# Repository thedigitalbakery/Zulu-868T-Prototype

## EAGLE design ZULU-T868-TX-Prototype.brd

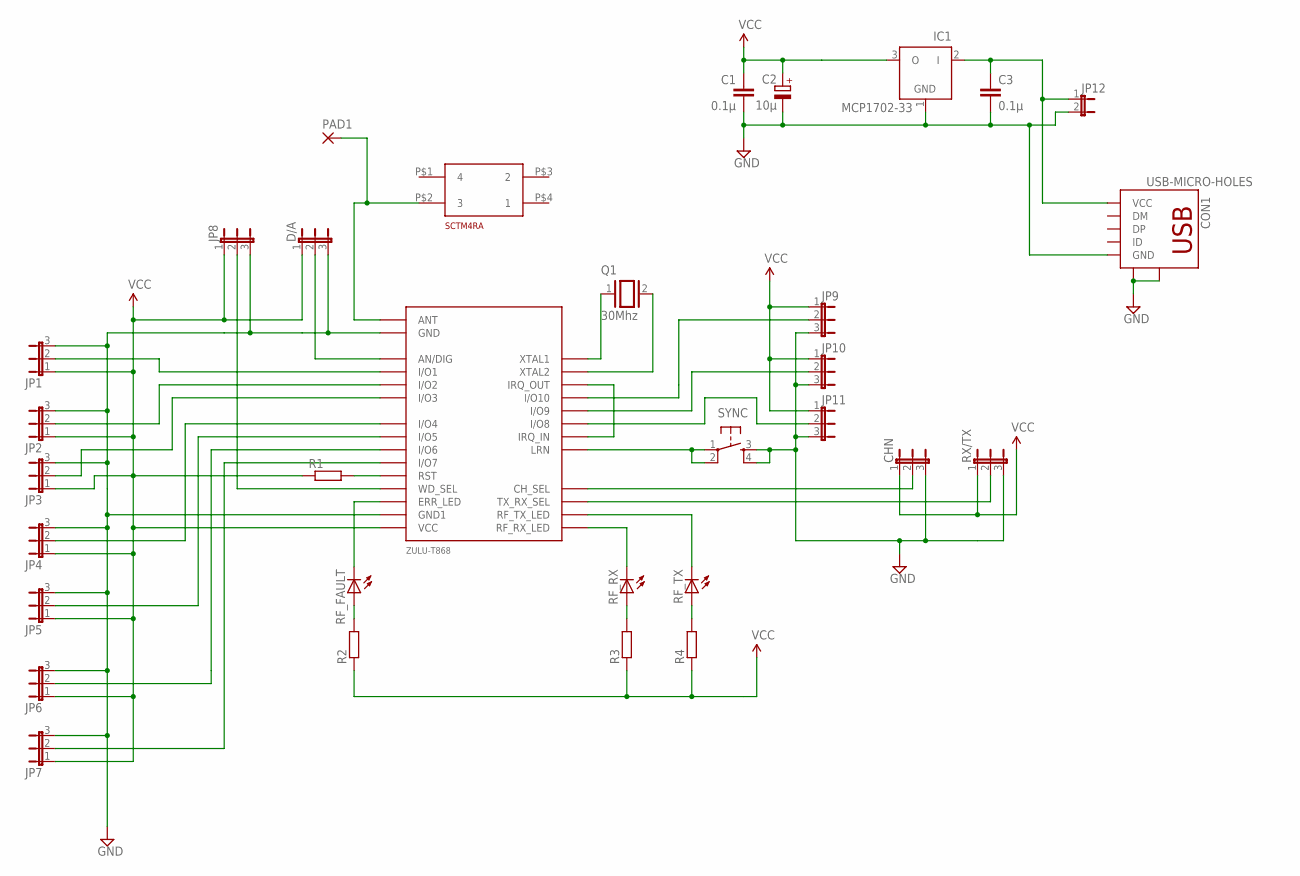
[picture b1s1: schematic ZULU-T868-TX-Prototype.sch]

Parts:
C1, C3: 0.1µ; C0805
C2: 10µ; E1,8-4
CHN: JP2E; JP2
CON1: USB-MICRO-HOLES; MICRO-USB-B-HOLES
D/A: JP2E; JP2
IC1: MCP1702-33; TO92
JP1, JP2, JP3, JP4, JP5, JP6, JP7, JP8, JP9, JP10, JP11: JP2E; JP2
JP12: JP1E; JP1
PAD1: 1,6/0,8
Q1: 30Mhz; QS
R1, R2, R3, R4: R-EU_M0805; M0805
RF_FAULT: LEDCHIPLED_0805; CHIPLED_0805
RF_RX: LEDCHIPLED_0805; CHIPLED_0805
RF_TX: LEDCHIPLED_0805; CHIPLED_0805
RX/TX: JP2E; JP2
SYNC: TAC_SWITCHPTH; TACTILE-PTH
U$1: SCTM4RA
U$2: ZULU-T868; ZULU-T-MODULE

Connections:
GND: C1.2, C2.-, C3.2, CHN.3, CON1.P$5 (GND), CON1.SHIELD1, CON1.SHIELD2, D/A.3, IC1.1 (GND), JP1.3, JP2.3, JP3.3, JP4.3, JP5.3, JP6.3, JP7.3, JP8.3, JP9.3, JP10.3, JP11.3, JP12.2, RX/TX.3, SYNC.3, SYNC.4, U$2.P$2 (GND), U$2.P$15 (GND1)
unnamed: D/A.2, U$2.P$3 (AN/DIG)
unnamed: Q1.1, U$2.P$30 (XTAL1)
unnamed: Q1.2, U$2.P$29 (XTAL2)
unnamed: R1.2, U$2.P$12 (RST)
unnamed: CHN.2, U$2.P$20 (CH_SEL)
unnamed: U$2.P$24 (IRQ_IN), U$2.P$28 (IRQ_OUT)
unnamed: RX/TX.2, U$2.P$19 (TX_RX_SEL)
unnamed: SYNC.1, SYNC.2, U$2.P$23 (LRN)
unnamed: RF_FAULT.C, U$2.P$14 (ERR_LED)
unnamed: JP2.2, U$2.P$5 (I/O2)
unnamed: JP1.2, U$2.P$4 (I/O1)
unnamed: C3.1, CON1.P$1 (VCC), IC1.2 (I), JP12.1
unnamed: R3.2, RF_RX.A
unnamed: R4.2, RF_TX.A
unnamed: RF_RX.C, U$2.P$17 (RF_RX_LED)
unnamed: RF_TX.C, U$2.P$18 (RF_TX_LED)
unnamed: JP6.2, U$2.P$10 (I/O6)
unnamed: R2.2, RF_FAULT.A
unnamed: JP3.2, U$2.P$6 (I/O3)
unnamed: JP4.2, U$2.P$8 (I/O4)
unnamed: JP5.2, U$2.P$9 (I/O5)
unnamed: JP7.2, U$2.P$11 (I/O7)
unnamed: JP11.2, U$2.P$25 (I/O8)
unnamed: JP10.2, U$2.P$26 (I/O9)
unnamed: JP9.2, U$2.P$27 (I/O10)
unnamed: PAD1.1, U$1.P$2 (3), U$2.P$1 (ANT)
unnamed: JP8.2, U$2.P$13 (WD_SEL)
VCC: C1.1, C2.+, CHN.1, D/A.1, IC1.3 (O), JP1.1, JP2.1, JP3.1, JP4.1, JP5.1, JP6.1, JP7.1, JP8.1, JP9.1, JP10.1, JP11.1, R1.1, R2.1, R3.1, R4.1, RX/TX.1, U$2.P$16 (VCC)

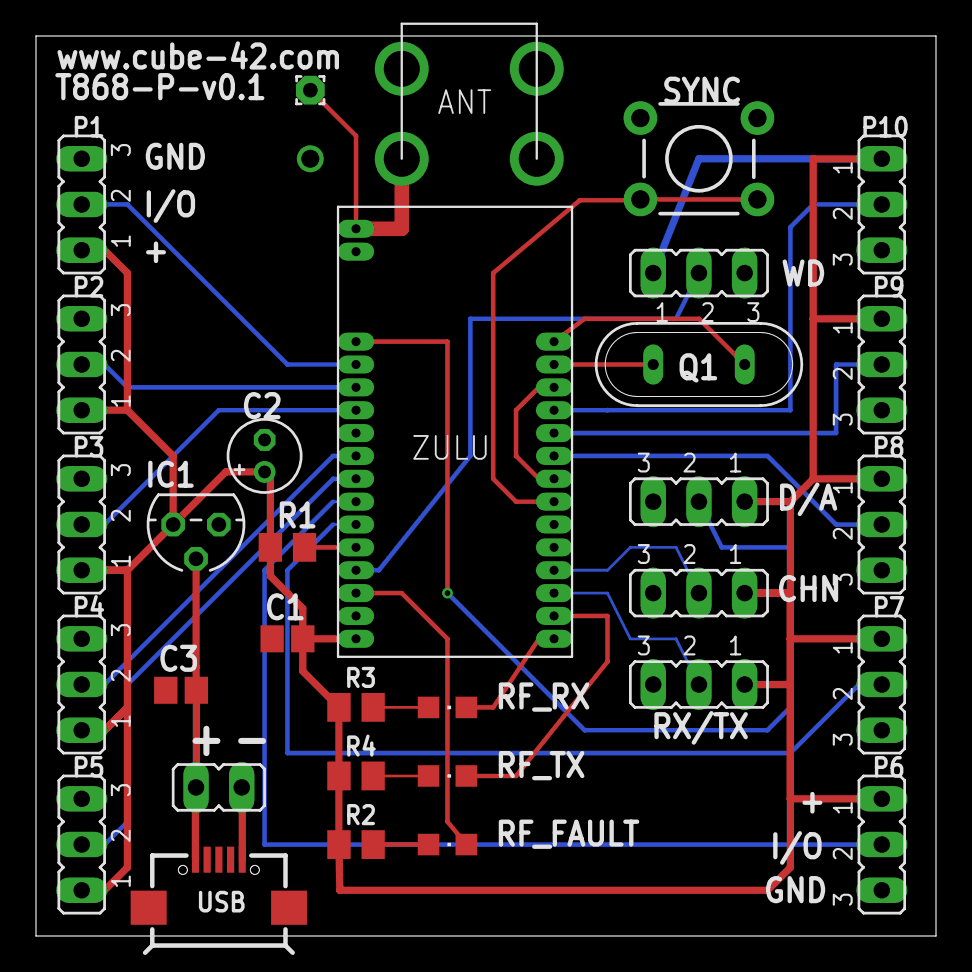
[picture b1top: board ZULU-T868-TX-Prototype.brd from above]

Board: 2 copper layers, 50.0 x 50.0 mm, 32 parts (0 on the bottom side), 29 nets.

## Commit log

2013-06-20 Initial prototype v0.1

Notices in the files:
parts and their libraries:
SparkFun-Electromechanical: Licensing: CC v3.0 Share-Alike You are welcome to use this library for commercial purposes.
